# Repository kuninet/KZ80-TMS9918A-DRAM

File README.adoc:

== KZ80シリーズ TMS9918A ビデオボード(DRAM版)

=== 概要
* SBC8080バスにつながるTMS9918Aビデオボードのプロジェクトです。
* 本ボードの詳しい説明は以下のwikiページをご覧ください。
** https://github.com/kuninet/KZ80-TMS9918A/wiki
* 以下のリポジトリからFORKしたかたちで、SRAM版からDRAM版へ変更したリポジトリです。
** https://github.com/kuninet/KZ80-TMS9918A

image::image/KZ80-TMS9918A.jpg[]

=== ライセンス
* 本プロジェクトのデータはMITライセンスのもとで公開します。

=== 参考
* 以下のサイトの情報を参考に作成しています。ありがとうございます。
** https://github.com/jblang/TMS9918A
** https://retrobrewcomputers.org/n8vem-pbwiki-archive/0/35845334/48860720/33053543/SRAM%20Replacement%20for%20TMS99x8%20VRAM.pdf

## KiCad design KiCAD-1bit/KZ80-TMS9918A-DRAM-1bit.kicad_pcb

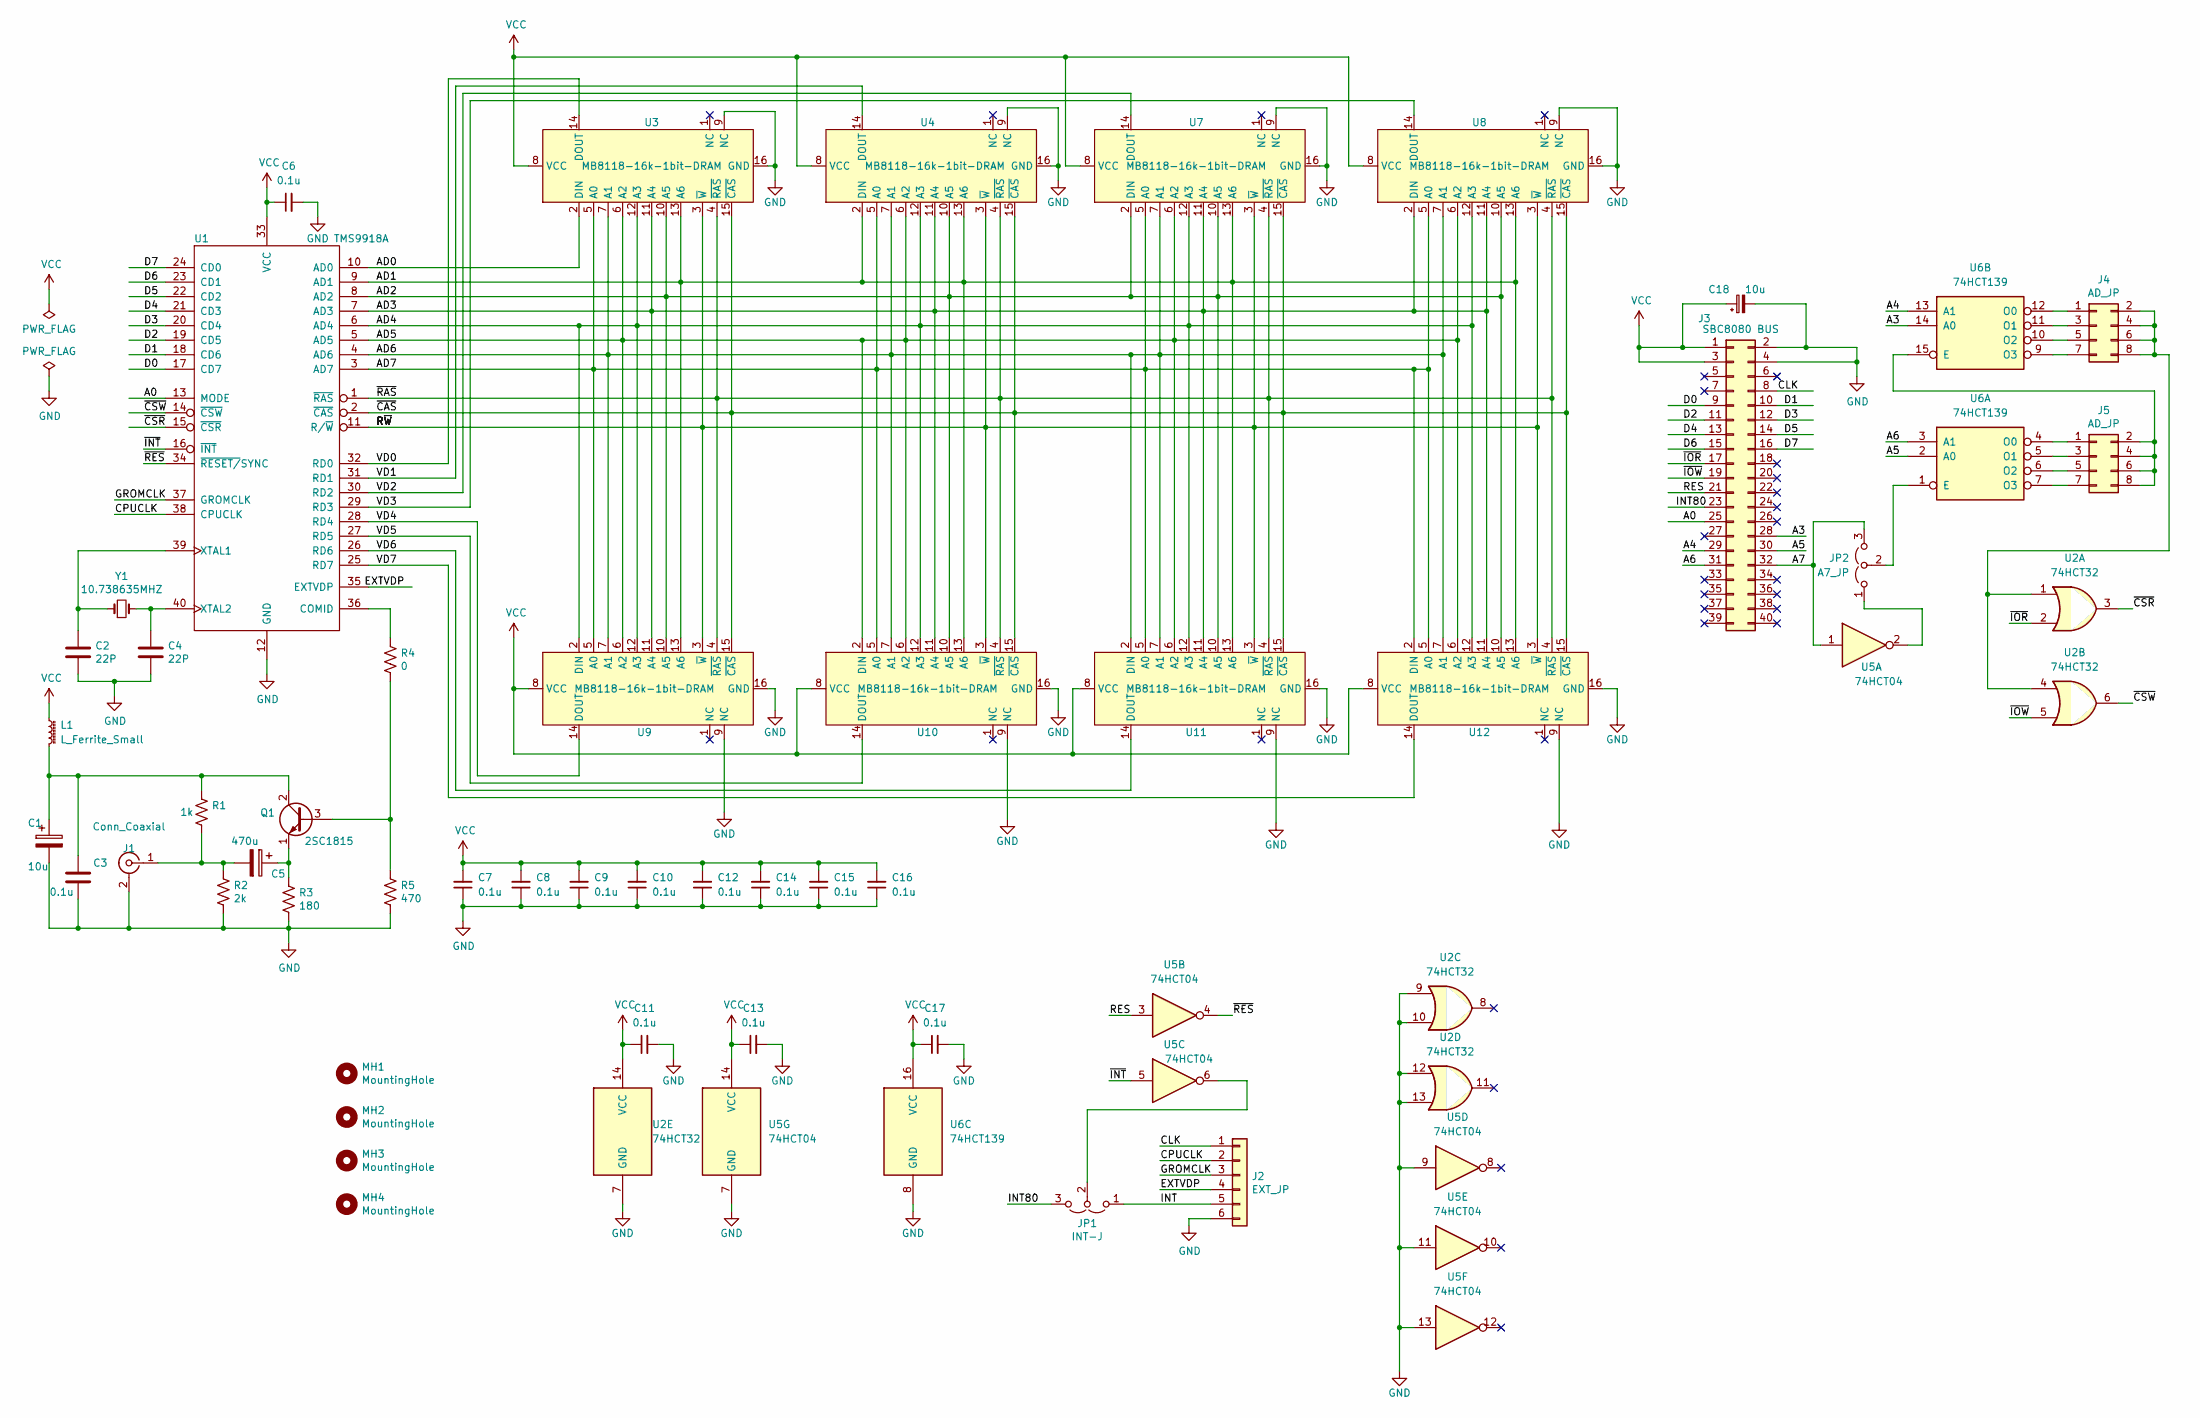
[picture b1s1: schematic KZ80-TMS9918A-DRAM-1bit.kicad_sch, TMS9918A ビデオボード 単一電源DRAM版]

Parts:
C1, C18: 10u; CP_Radial_D5.0mm_P2.50mm
C2, C4: 22P; C_Disc_D3.0mm_W1.6mm_P2.50mm
C3, C6, C7, C8, C9, C10, C11, C12, C13, C14, C15, C16, C17: 0.1u; C_Disc_D3.0mm_W1.6mm_P2.50mm
C5: 470u; CP_Radial_D5.0mm_P2.50mm
J1: Conn_Coaxial; RCAConAE
J2: EXT_JP; PinHeader_1x06_P2.54mm_Horizontal
J3: SBC8080 BUS; PinHeader_2x20_P2.54mm_Horizontal
J4, J5: AD_JP; PinHeader_2x04_P2.54mm_Vertical
JP1: INT-J; PinHeader_1x03_P2.54mm_Vertical
JP2: A7_JP; PinHeader_1x03_P2.54mm_Vertical
L1: L_Ferrite_Small; R_Axial_DIN0207_L6.3mm_D2.5mm_P10.16mm_Horizontal
MH1, MH2, MH3, MH4: MountingHole; MountingHole_3.2mm_M3
Q1: 2SC1815; TO-92_Inline_Wide
R1: 1k; R_Axial_DIN0207_L6.3mm_D2.5mm_P10.16mm_Horizontal
R2: 2k; R_Axial_DIN0207_L6.3mm_D2.5mm_P10.16mm_Horizontal
R3: 180; R_Axial_DIN0207_L6.3mm_D2.5mm_P10.16mm_Horizontal
R4: 0; R_Axial_DIN0207_L6.3mm_D2.5mm_P10.16mm_Horizontal
R5: 470; R_Axial_DIN0207_L6.3mm_D2.5mm_P10.16mm_Horizontal
U1: TMS9918A; DIP-40_W15.24mm_Socket
U2: 74HCT32; DIP-14_W7.62mm_Socket
U3, U4, U7, U8, U9, U10, U11, U12: MB8118-16k-1bit-DRAM; DIP-16_W7.62mm_Socket
U5: 74HCT04; DIP-14_W7.62mm_Socket
U6: 74HCT139; DIP-16_W7.62mm_Socket
Y1: 10.738635MHZ; Crystal_HC49-U_Vertical

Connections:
/A0: J3.25, U1.13 (MODE)
/A3: J3.28, U6.14 (A0)
/A4: J3.29, U6.13 (A1)
/A5: J3.30, U6.2 (A0)
/A6: J3.31, U6.3 (A1)
/A7: J3.32, JP2.3 (B), U5.1
/AD0: U1.10 (AD0), U3.2 (DIN)
/AD1: U1.9 (AD1), U3.13 (A6), U4.2 (DIN), U4.13 (A6), U7.13 (A6), U8.13 (A6), U9.13 (A6), U10.13 (A6), U11.13 (A6), U12.13 (A6)
/AD2: U1.8 (AD2), U3.10 (A5), U4.10 (A5), U7.2 (DIN), U7.10 (A5), U8.10 (A5), U9.10 (A5), U10.10 (A5), U11.10 (A5), U12.10 (A5)
/AD3: U1.7 (AD3), U3.11 (A4), U4.11 (A4), U7.11 (A4), U8.2 (DIN), U8.11 (A4), U9.11 (A4), U10.11 (A4), U11.11 (A4), U12.11 (A4)
/AD4: U1.6 (AD4), U3.12 (A3), U4.12 (A3), U7.12 (A3), U8.12 (A3), U9.2 (DIN), U9.12 (A3), U10.12 (A3), U11.12 (A3), U12.12 (A3)
/AD5: U1.5 (AD5), U3.6 (A2), U4.6 (A2), U7.6 (A2), U8.6 (A2), U9.6 (A2), U10.2 (DIN), U10.6 (A2), U11.6 (A2), U12.6 (A2)
/AD6: U1.4 (AD6), U3.7 (A1), U4.7 (A1), U7.7 (A1), U8.7 (A1), U9.7 (A1), U10.7 (A1), U11.2 (DIN), U11.7 (A1), U12.7 (A1)
/AD7: U1.3 (AD7), U3.5 (A0), U4.5 (A0), U7.5 (A0), U8.5 (A0), U9.5 (A0), U10.5 (A0), U11.5 (A0), U12.2 (DIN), U12.5 (A0)
/CLK: J2.1, J3.8
/CPUCLK: J2.2, U1.38 (CPUCLK)
/D0: J3.9, U1.17 (CD7)
/D1: J3.10, U1.18 (CD6)
/D2: J3.11, U1.19 (CD5)
/D3: J3.12, U1.20 (CD4)
/D4: J3.13, U1.21 (CD3)
/D5: J3.14, U1.22 (CD2)
/D6: J3.15, U1.23 (CD1)
/D7: J3.16, U1.24 (CD0)
/EXTVDP: J2.4, U1.35 (EXTVDP)
/GROMCLK: J2.3, U1.37 (GROMCLK)
/INT: J2.5, JP1.1 (A)
/INT80: J3.23, JP1.3 (B)
/RES: J3.21, U5.3
/R~W: U1.11 (R/~W), U3.3 (~W), U4.3 (~W), U7.3 (~W), U8.3 (~W), U9.3 (~W), U10.3 (~W), U11.3 (~W), U12.3 (~W)
/VD0: U1.32 (RD0), U3.14 (DOUT)
/VD1: U1.31 (RD1), U4.14 (DOUT)
/VD2: U1.30 (RD2), U7.14 (DOUT)
/VD3: U1.29 (RD3), U8.14 (DOUT)
/VD4: U1.28 (RD4), U9.14 (DOUT)
/VD5: U1.27 (RD5), U10.14 (DOUT)
/VD6: U1.26 (RD6), U11.14 (DOUT)
/VD7: U1.25 (RD7), U12.14 (DOUT)
/~CAS: U1.2 (~CAS), U3.15 (~CAS), U4.15 (~CAS), U7.15 (~CAS), U8.15 (~CAS), U9.15 (~CAS), U10.15 (~CAS), U11.15 (~CAS), U12.15 (~CAS)
/~CSR: U1.15 (~CSR), U2.3
/~CSW: U1.14 (~CSW), U2.6
/~INT: U1.16 (~INT), U5.5
/~IOR: J3.17, U2.2
/~IOW: J3.19, U2.5
/~RAS: U1.1 (~RAS), U3.4 (~RAS), U4.4 (~RAS), U7.4 (~RAS), U8.4 (~RAS), U9.4 (~RAS), U10.4 (~RAS), U11.4 (~RAS), U12.4 (~RAS)
/~RES: U1.34 (~RESET/SYNC), U5.4
GND: C1.2, C2.2, C3.2, C4.2, C6.2, C7.1, C8.1, C9.1, C10.1, C11.2, C12.1, C13.2, C14.1, C15.1, C16.1, C17.2, C18.2, J1.2 (Ext), J2.6, J3.2, J3.4, R2.2, R3.2, R5.2, U1.12 (GND), U2.7 (GND), U2.9, U2.10, U2.12, U2.13, U3.9 (NC), U3.16 (GND), U4.9 (NC), U4.16 (GND), U5.7 (GND), U5.9, U5.11, U5.13, U6.8 (GND), U7.9 (NC), U7.16 (GND), U8.9 (NC), U8.16 (GND), U9.9 (NC), U9.16 (GND), U10.9 (NC), U10.16 (GND), U11.9 (NC), U11.16 (GND), U12.9 (NC), U12.16 (GND)
unnamed: C5.2, J1.1 (In), R1.2, R2.1
unnamed: J4.1, U6.12 (O0)
unnamed: J4.2, J4.4, J4.6, J4.8, U2.1, U2.4
unnamed: J4.3, U6.11 (O1)
unnamed: J4.5, U6.10 (O2)
unnamed: J4.7, U6.9 (O3)
unnamed: J5.1, U6.4 (O0)
unnamed: J5.2, J5.4, J5.6, J5.8, U6.15 (E)
unnamed: J5.3, U6.5 (O1)
unnamed: J5.5, U6.6 (O2)
unnamed: J5.7, U6.7 (O3)
unnamed: JP1.2 (C), U5.6
unnamed: JP2.1 (A), U5.2
unnamed: JP2.2 (C), U6.1 (E)
unnamed: Q1.3 (B), R4.2, R5.1
unnamed: C1.1, C3.1, L1.2, Q1.2 (C), R1.1
unnamed: C5.1, Q1.1 (E), R3.1
unnamed: R4.1, U1.36 (COMID)
unnamed: C2.1, U1.39 (XTAL1), Y1.1
unnamed: C4.1, U1.40 (XTAL2), Y1.2
VCC: C6.1, C7.2, C8.2, C9.2, C10.2, C11.1, C12.2, C13.1, C14.2, C15.2, C16.2, C17.1, C18.1, J3.1, J3.3, L1.1, U1.33 (VCC), U2.14 (VCC), U3.8 (VCC), U4.8 (VCC), U5.14 (VCC), U6.16 (VCC), U7.8 (VCC), U8.8 (VCC), U9.8 (VCC), U10.8 (VCC), U11.8 (VCC), U12.8 (VCC)

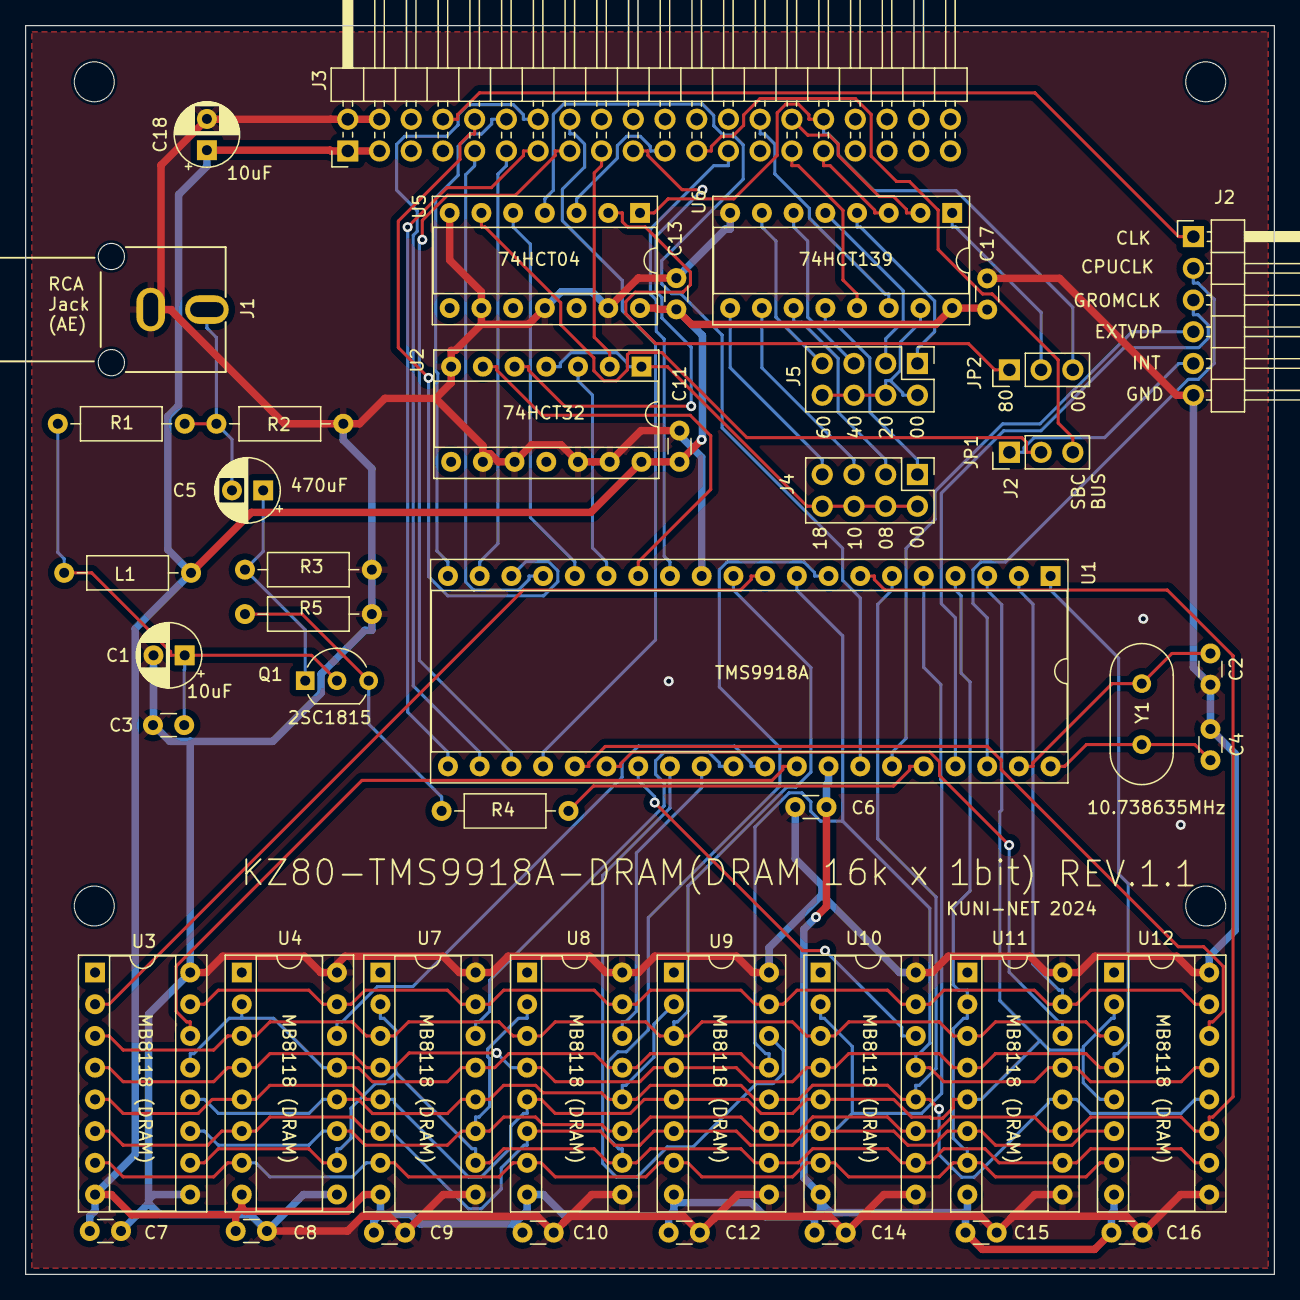
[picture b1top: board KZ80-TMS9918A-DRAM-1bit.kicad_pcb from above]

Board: 2 copper layers, 100.0 x 100.0 mm, 49 parts (0 on the bottom side), 68 nets.

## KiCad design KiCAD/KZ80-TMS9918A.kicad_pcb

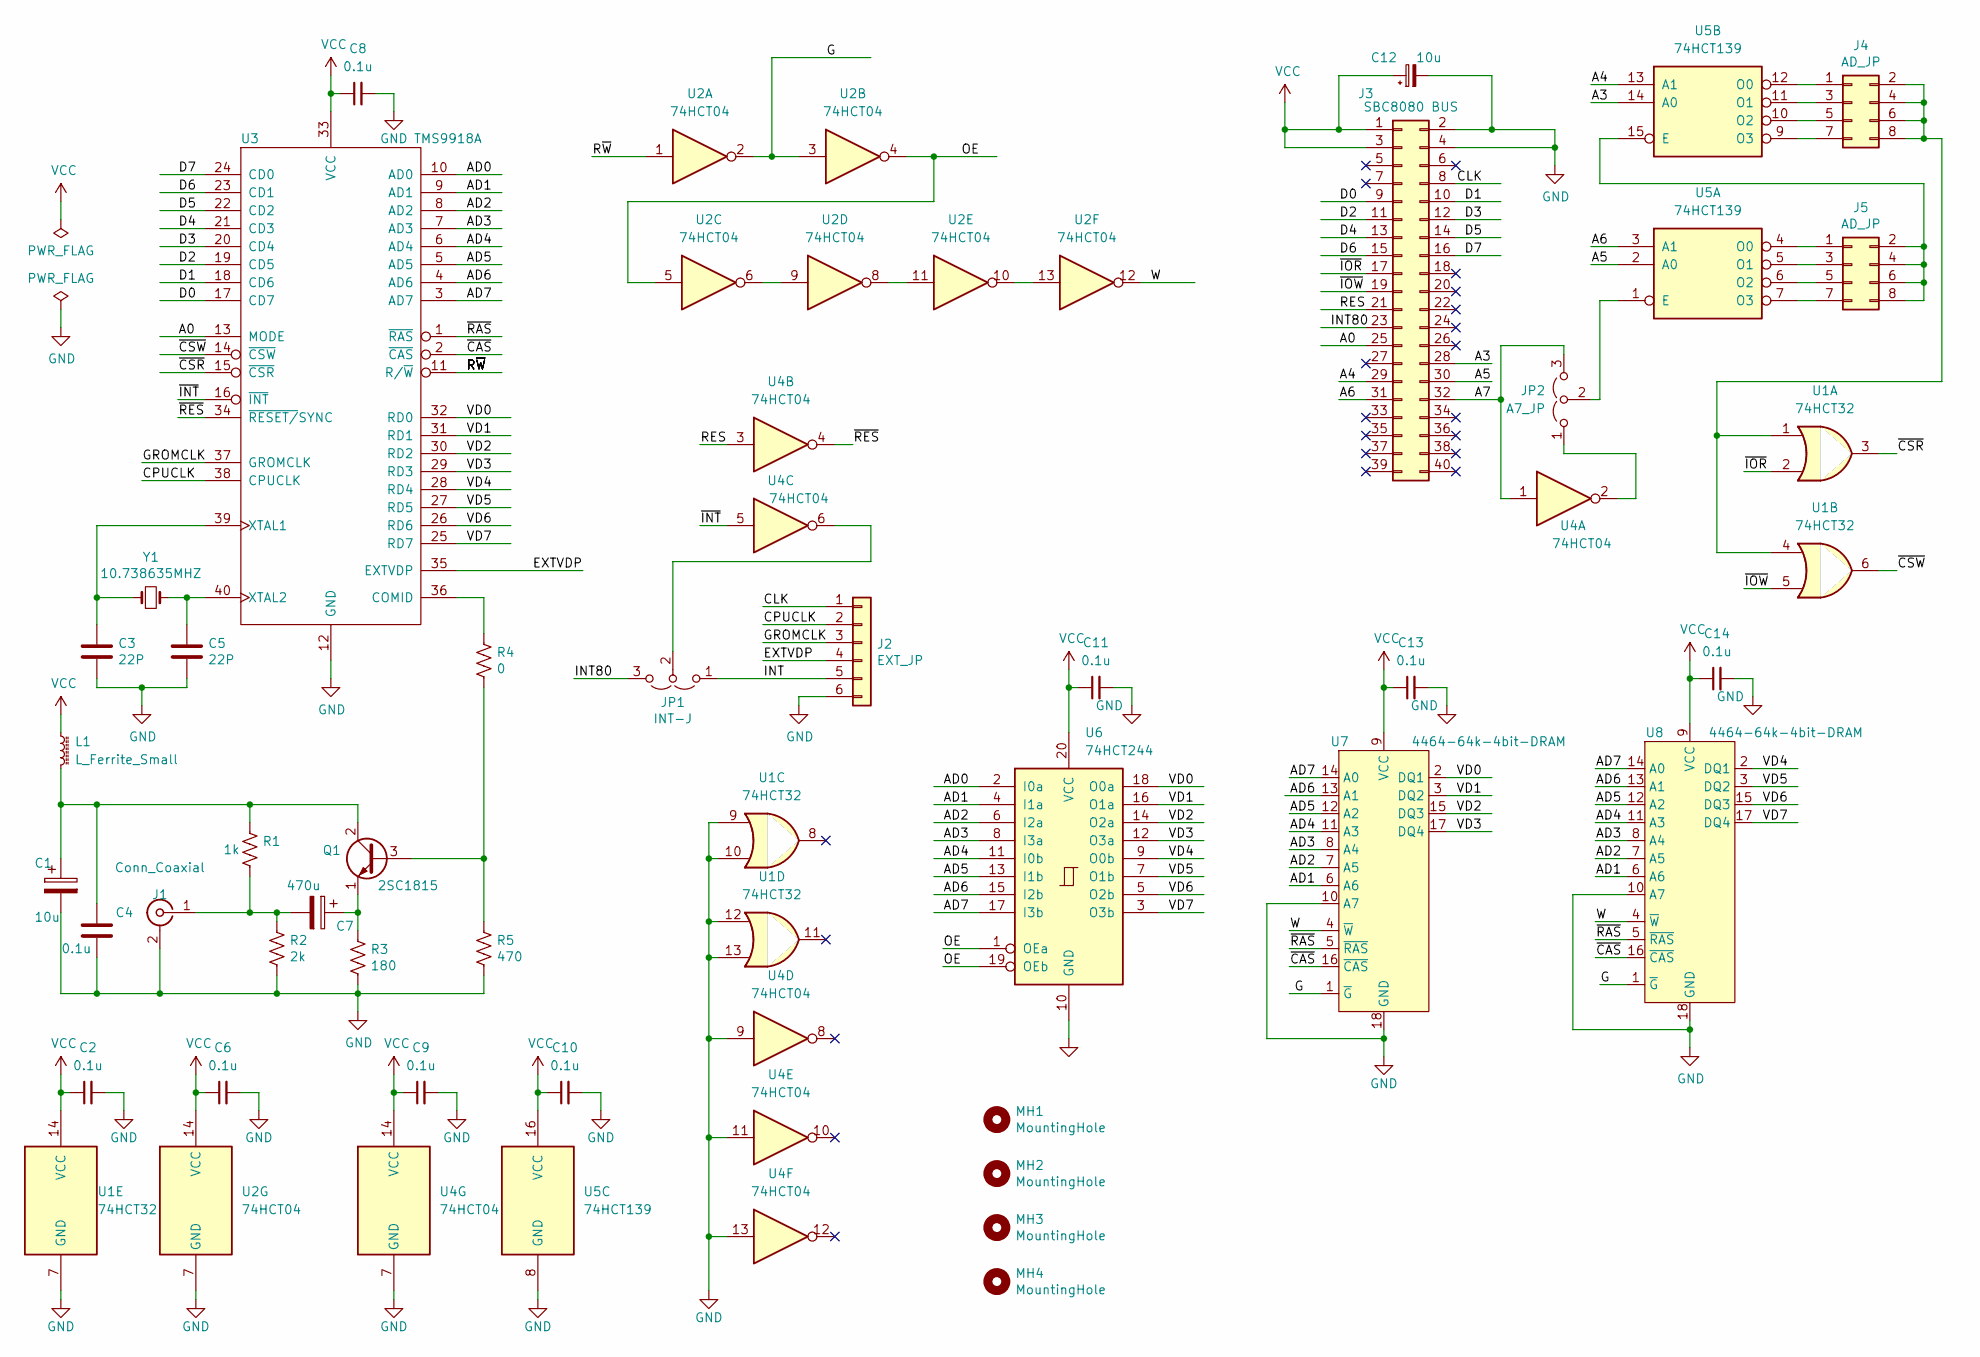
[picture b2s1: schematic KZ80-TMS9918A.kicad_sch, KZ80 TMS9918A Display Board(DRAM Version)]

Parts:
C1, C12: 10u; CP_Radial_D5.0mm_P2.50mm
C2, C4, C6, C8, C9, C10, C11, C13, C14: 0.1u; C_Disc_D3.0mm_W1.6mm_P2.50mm
C3, C5: 22P; C_Disc_D3.0mm_W1.6mm_P2.50mm
C7: 470u; CP_Radial_D5.0mm_P2.50mm
J1: Conn_Coaxial; RCAConAE
J2: EXT_JP; PinHeader_1x06_P2.54mm_Horizontal
J3: SBC8080 BUS; PinHeader_2x20_P2.54mm_Horizontal
J4, J5: AD_JP; PinHeader_2x04_P2.54mm_Vertical
JP1: INT-J; PinHeader_1x03_P2.54mm_Vertical
JP2: A7_JP; PinHeader_1x03_P2.54mm_Vertical
L1: L_Ferrite_Small; R_Axial_DIN0207_L6.3mm_D2.5mm_P10.16mm_Horizontal
MH1, MH2, MH3, MH4: MountingHole; MountingHole_3.2mm_M3
Q1: 2SC1815; TO-92_Inline_Wide
R1: 1k; R_Axial_DIN0207_L6.3mm_D2.5mm_P10.16mm_Horizontal
R2: 2k; R_Axial_DIN0207_L6.3mm_D2.5mm_P10.16mm_Horizontal
R3: 180; R_Axial_DIN0207_L6.3mm_D2.5mm_P10.16mm_Horizontal
R4: 0; R_Axial_DIN0207_L6.3mm_D2.5mm_P10.16mm_Horizontal
R5: 470; R_Axial_DIN0207_L6.3mm_D2.5mm_P10.16mm_Horizontal
U1: 74HCT32; DIP-14_W7.62mm_Socket
U2, U4: 74HCT04; DIP-14_W7.62mm_Socket
U3: TMS9918A; DIP-40_W15.24mm_Socket
U5: 74HCT139; DIP-16_W7.62mm_Socket
U6: 74HCT244; DIP-20_W7.62mm_Socket
U7, U8: 4464-64k-4bit-DRAM; DIP-18_W7.62mm_Socket
Y1: 10.738635MHZ; Crystal_HC49-U_Vertical

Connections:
/A0: J3.25, U3.13 (MODE)
/A3: J3.28, U5.14 (A0)
/A4: J3.29, U5.13 (A1)
/A5: J3.30, U5.2 (A0)
/A6: J3.31, U5.3 (A1)
/A7: J3.32, JP2.3 (B), U4.1
/AD0: U3.10 (AD0), U6.2 (I0a)
/AD1: U3.9 (AD1), U6.4 (I1a), U7.6 (A6), U8.6 (A6)
/AD2: U3.8 (AD2), U6.6 (I2a), U7.7 (A5), U8.7 (A5)
/AD3: U3.7 (AD3), U6.8 (I3a), U7.8 (A4), U8.8 (A4)
/AD4: U3.6 (AD4), U6.11 (I0b), U7.11 (A3), U8.11 (A3)
/AD5: U3.5 (AD5), U6.13 (I1b), U7.12 (A2), U8.12 (A2)
/AD6: U3.4 (AD6), U6.15 (I2b), U7.13 (A1), U8.13 (A1)
/AD7: U3.3 (AD7), U6.17 (I3b), U7.14 (A0), U8.14 (A0)
/CLK: J2.1, J3.8
/CPUCLK: J2.2, U3.38 (CPUCLK)
/D0: J3.9, U3.17 (CD7)
/D1: J3.10, U3.18 (CD6)
/D2: J3.11, U3.19 (CD5)
/D3: J3.12, U3.20 (CD4)
/D4: J3.13, U3.21 (CD3)
/D5: J3.14, U3.22 (CD2)
/D6: J3.15, U3.23 (CD1)
/D7: J3.16, U3.24 (CD0)
/EXTVDP: J2.4, U3.35 (EXTVDP)
/G: U2.2, U2.3, U7.1 (~G), U8.1 (~G)
/GROMCLK: J2.3, U3.37 (GROMCLK)
/INT: J2.5, JP1.1 (A)
/INT80: J3.23, JP1.3 (B)
/OE: U2.4, U2.5, U6.1 (OEa), U6.19 (OEb)
/RES: J3.21, U4.3
/R~W: U2.1, U3.11 (R/~W)
/VD0: U3.32 (RD0), U6.18 (O0a), U7.2 (DQ1)
/VD1: U3.31 (RD1), U6.16 (O1a), U7.3 (DQ2)
/VD2: U3.30 (RD2), U6.14 (O2a), U7.15 (DQ3)
/VD3: U3.29 (RD3), U6.12 (O3a), U7.17 (DQ4)
/VD4: U3.28 (RD4), U6.9 (O0b), U8.2 (DQ1)
/VD5: U3.27 (RD5), U6.7 (O1b), U8.3 (DQ2)
/VD6: U3.26 (RD6), U6.5 (O2b), U8.15 (DQ3)
/VD7: U3.25 (RD7), U6.3 (O3b), U8.17 (DQ4)
/W: U2.12, U7.4 (~W), U8.4 (~W)
/~CAS: U3.2 (~CAS), U7.16 (~CAS), U8.16 (~CAS)
/~CSR: U1.3, U3.15 (~CSR)
/~CSW: U1.6, U3.14 (~CSW)
/~INT: U3.16 (~INT), U4.5
/~IOR: J3.17, U1.2
/~IOW: J3.19, U1.5
/~RAS: U3.1 (~RAS), U7.5 (~RAS), U8.5 (~RAS)
/~RES: U3.34 (~RESET/SYNC), U4.4
GND: C1.2, C2.2, C3.2, C4.2, C5.2, C6.2, C8.2, C9.2, C10.2, C11.2, C12.2, C13.2, C14.2, J1.2 (Ext), J2.6, J3.2, J3.4, R2.2, R3.2, R5.2, U1.7 (GND), U1.9, U1.10, U1.12, U1.13, U2.7 (GND), U3.12 (GND), U4.7 (GND), U4.9, U4.11, U4.13, U5.8 (GND), U6.10 (GND), U7.10 (A7), U7.18 (GND), U8.10 (A7), U8.18 (GND)
unnamed: C7.2, J1.1 (In), R1.2, R2.1
unnamed: J4.1, U5.12 (O0)
unnamed: J4.2, J4.4, J4.6, J4.8, U1.1, U1.4
unnamed: J4.3, U5.11 (O1)
unnamed: J4.5, U5.10 (O2)
unnamed: J4.7, U5.9 (O3)
unnamed: J5.1, U5.4 (O0)
unnamed: J5.2, J5.4, J5.6, J5.8, U5.15 (E)
unnamed: J5.3, U5.5 (O1)
unnamed: J5.5, U5.6 (O2)
unnamed: J5.7, U5.7 (O3)
unnamed: JP1.2 (C), U4.6
unnamed: JP2.1 (A), U4.2
unnamed: JP2.2 (C), U5.1 (E)
unnamed: Q1.3 (B), R4.2, R5.1
unnamed: C1.1, C4.1, L1.2, Q1.2 (C), R1.1
unnamed: C7.1, Q1.1 (E), R3.1
unnamed: U2.6, U2.9
unnamed: U2.10, U2.13
unnamed: U2.8, U2.11
unnamed: R4.1, U3.36 (COMID)
unnamed: C3.1, U3.39 (XTAL1), Y1.1
unnamed: C5.1, U3.40 (XTAL2), Y1.2
VCC: C2.1, C6.1, C8.1, C9.1, C10.1, C11.1, C12.1, C13.1, C14.1, J3.1, J3.3, L1.1, U1.14 (VCC), U2.14 (VCC), U3.33 (VCC), U4.14 (VCC), U5.16 (VCC), U6.20 (VCC), U7.9 (VCC), U8.9 (VCC)

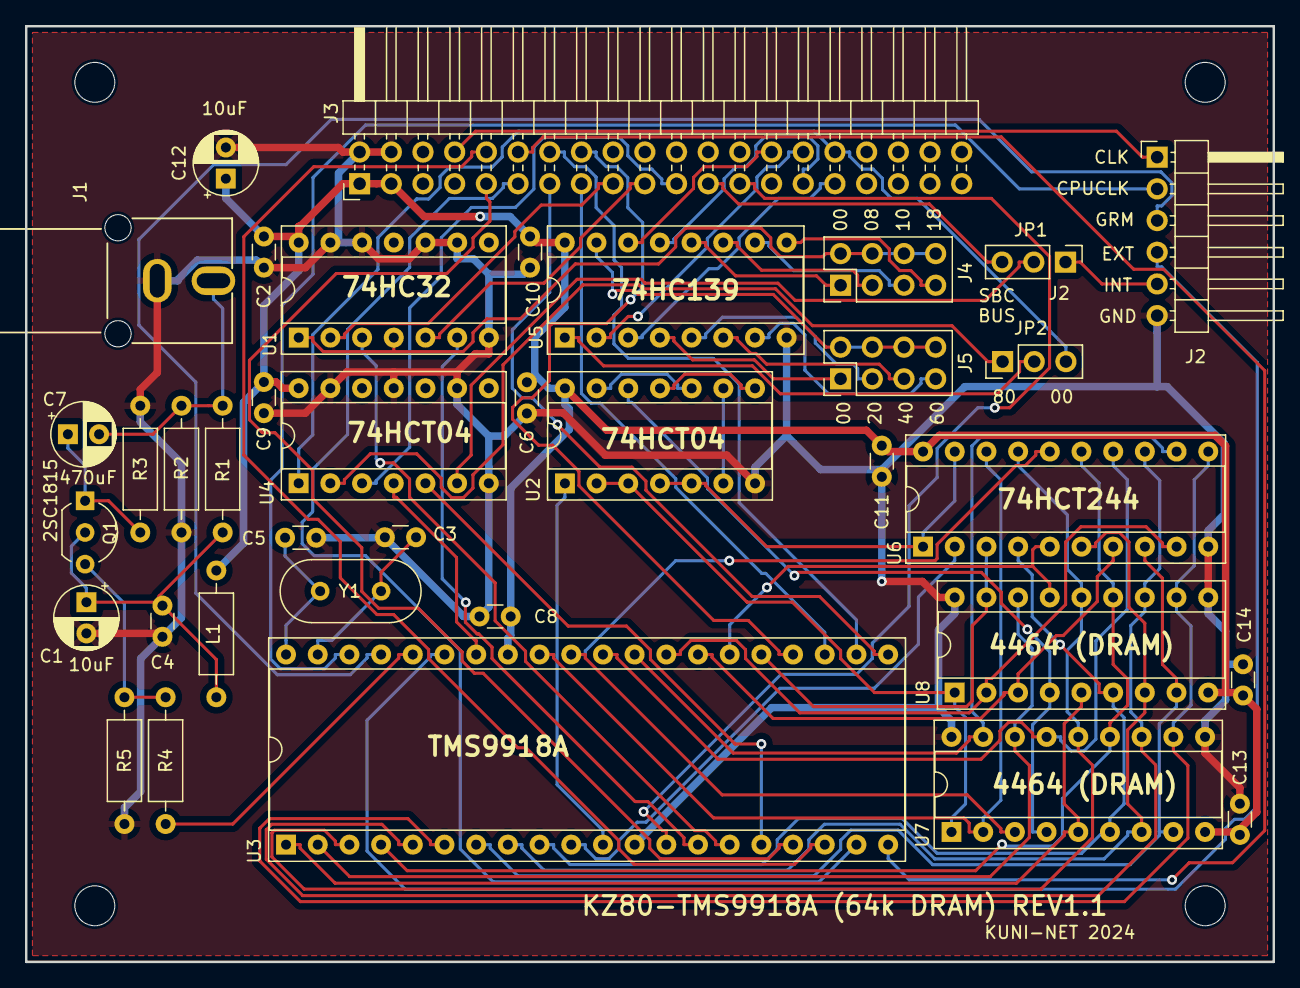
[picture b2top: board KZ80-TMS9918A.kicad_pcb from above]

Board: 2 copper layers, 100.0 x 75.0 mm, 41 parts (0 on the bottom side), 74 nets.

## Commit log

2022-08-29 DRAM回路図作成 ベータ版
2023-12-23 4464 DRAM対応
2023-12-23 パスコン追加等
2023-12-23 16k x 1bit版 回路図など作成
2023-12-24 回路図バグ修正
2024-01-01 回路図イメージデータ再出力
2024-01-01 DRAM 16kx1bit版プリントパターン作成
2024-01-03 64k DRAM版 ガーバー出力
2024-02-12 シルク印刷間違い修正(64bit、16kbit両方) REV1.1ガーバー出力
2024-02-12 部品表整備
2024-02-12 README修正
2024-02-12 READMEにジャンパ設定追加
2024-02-18 64k版 部品配置調整、16k版 4164 DRAM対応版 ガーバーデータ出力
2024-02-18 16k版 回路図PDF/jpeg 差し替え
